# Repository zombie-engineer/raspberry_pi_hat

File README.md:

Raspberry PI hat.

Convenience expansion board for raspberry pi development.

Features:

JTAG connector for debug
Raspberry Pi has JTAG pins, TDO, TDI, TMS, TCK, etc. They are distributed in chaotic way across pin connector.
For this reason it is good to create a nice little connector, especially designated for JTAG

Micro USB connector for uart output
Raspberry PI has special pins for UART. This pins are routed to FTDI FT232H chip, which further redirects uart
data to USB.
Datasheet for the FTDI FT232H is here:
https://ftdichip.com/wp-content/uploads/2024/09/DS_FT232H.pdf

Display connector for ILI9341 SPI Display

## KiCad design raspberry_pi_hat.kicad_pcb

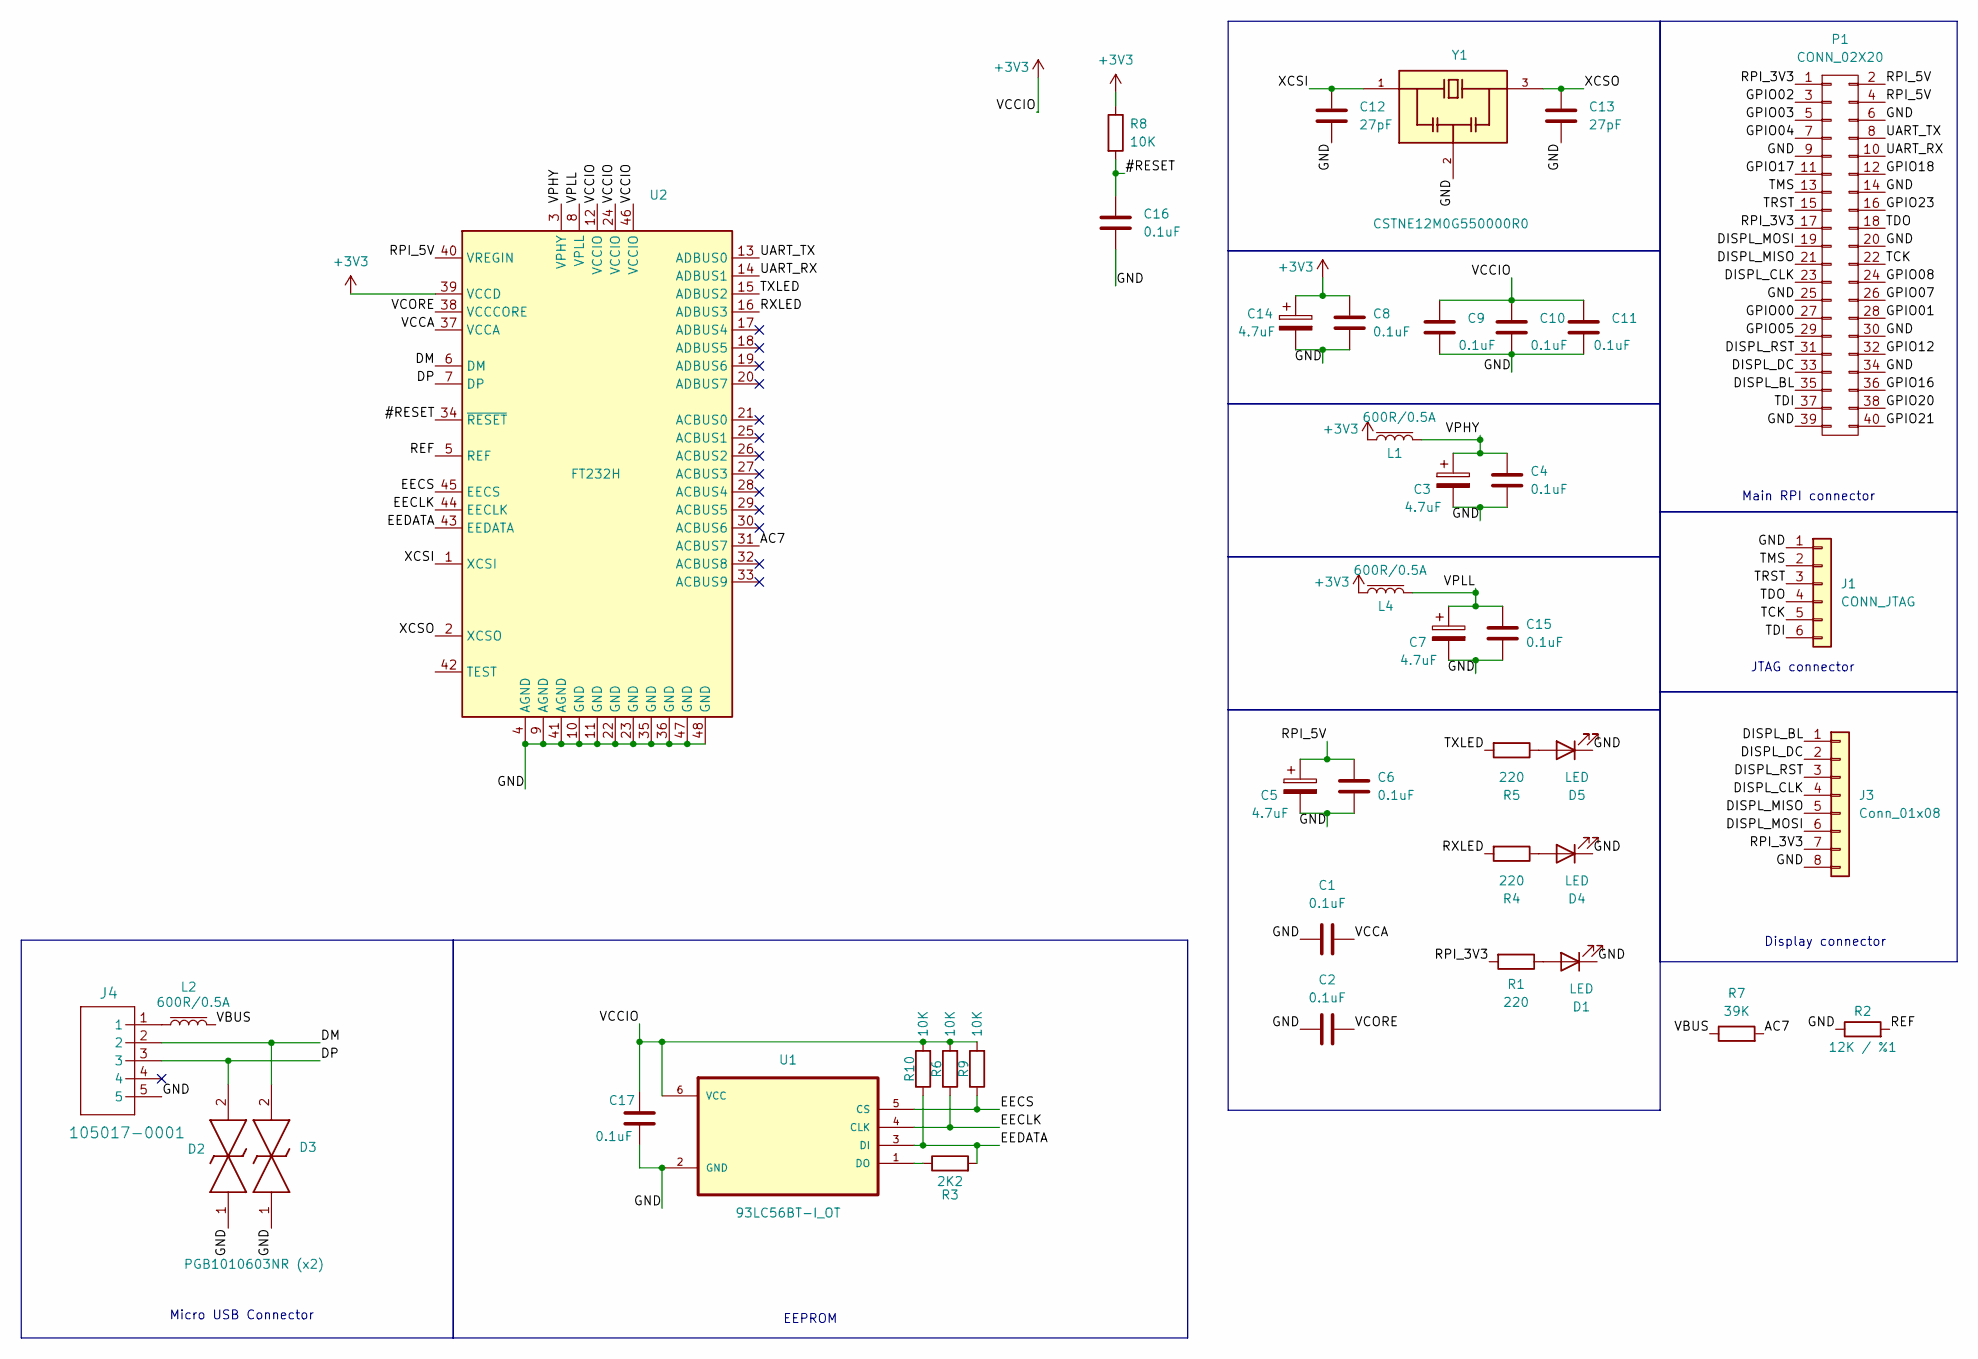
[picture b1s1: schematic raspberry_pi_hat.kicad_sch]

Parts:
C1, C2, C4, C6, C8, C9, C10, C11, C15, C16, C17: 0.1uF; C_0201_0603Metric_Pad0.64x0.40mm_HandSolder
C3, C5, C7, C14: 4.7uF; CAPPM2014X120N
C12, C13: 27pF; C_0201_0603Metric_Pad0.64x0.40mm_HandSolder
D1, D4, D5: LED; LED_0603_1608Metric
D2: PGB1010603NR (x2); PGB1010603NRHF; Mouser Part Number 576-PGB1010603NR
D3: PGB1010603NR; PGB1010603NRHF; Mouser Part Number 576-PGB1010603NR
J1: CONN_JTAG; PinSocket_1x06_P2.54mm_Horizontal
J3: Conn_01x08; PinHeader_1x08_P2.54mm_Horizontal
J4: 105017-0001; CON00363_5_MOL_FIXED
L1, L2, L4: 600R/0.5A; BLM21AG102BH1J
P1: CONN_02X20; PinSocket_2x20_P2.54mm_Vertical
R1, R4, R5: 220; R_0201_0603Metric_Pad0.64x0.40mm_HandSolder
R2: 12K / %1; R_0201_0603Metric_Pad0.64x0.40mm_HandSolder
R3: 2K2; R_0201_0603Metric_Pad0.64x0.40mm_HandSolder
R6, R8, R9, R10: 10K; R_0201_0603Metric_Pad0.64x0.40mm_HandSolder
R7: 39K; R_0201_0603Metric_Pad0.64x0.40mm_HandSolder
U1: 93LC56BT-I_OT; SOT95P280X145-6N
U2: FT232H; QFP50P900X900X160-48N
Y1: CSTNE12M0G550000R0; OSC_CSTNE12M0G550000R0; PARTREV JGC42-8858A

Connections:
+3V3: C8.1, C9.1, C10.1, C11.1, C14.1, C17.1, L1.1, L4.1, R6.2, R8.1, R9.2, R10.2, U1.6 (VCC), U2.12 (VCCIO), U2.24 (VCCIO), U2.39 (VCCD), U2.46 (VCCIO)
/#RESET: C16.1, R8.2, U2.34 (~RESET)
/AC7: R7.2, U2.31 (ACBUS7)
/DISPL_BL: J3.1, P1.35
/DISPL_CLK: J3.4, P1.23
/DISPL_DC: J3.2, P1.33
/DISPL_MISO: J3.5, P1.21
/DISPL_MOSI: J3.6, P1.19
/DISPL_RST: J3.3, P1.31
/DM: D3.2, J4.2, U2.6 (DM)
/DP: D2.2, J4.3, U2.7 (DP)
/EECLK: R6.1, U1.4 (CLK), U2.44 (EECLK)
/EECS: R9.1, U1.5 (CS), U2.45 (EECS)
/EEDATA: R3.2, R10.1, U1.3 (DI), U2.43 (EEDATA)
/GND: C1.1, C2.1, C3.2, C4.2, C5.2, C6.2, C7.2, C8.2, C9.2, C10.2, C11.2, C12.1, C13.1, C14.2, C15.2, C16.2, C17.2, D1.1 (K), D2.1, D3.1, D4.1 (K), D5.1 (K), J1.1, J3.8, J4.5, P1.6, P1.9, P1.14, P1.20, P1.25, P1.30, P1.34, P1.39, R2.1, U1.2 (GND), U2.4 (AGND), U2.9 (AGND), U2.10 (GND), U2.11 (GND), U2.22 (GND), U2.23 (GND), U2.35 (GND), U2.36 (GND), U2.41 (AGND), U2.47 (GND), U2.48 (GND), Y1.2
/GPIO00: P1.27
/GPIO01: P1.28
/GPIO02: P1.3
/GPIO03: P1.5
/GPIO04: P1.7
/GPIO05: P1.29
/GPIO07: P1.26
/GPIO08: P1.24
/GPIO12: P1.32
/GPIO16: P1.36
/GPIO17: P1.11
/GPIO18: P1.12
/GPIO20: P1.38
/GPIO21: P1.40
/GPIO23: P1.16
/REF: R2.2, U2.5 (REF)
/RPI_3V3: J3.7, P1.1, P1.17, R1.2
/RPI_5V: C5.1, C6.1, P1.2, P1.4, U2.40 (VREGIN)
/RXLED: R4.2, U2.16 (ADBUS3)
/TCK: J1.5, P1.22
/TDI: J1.6, P1.37
/TDO: J1.4, P1.18
/TMS: J1.2, P1.13
/TRST: J1.3, P1.15
/TXLED: R5.2, U2.15 (ADBUS2)
/UART_RX: P1.10, U2.14 (ADBUS1)
/UART_TX: P1.8, U2.13 (ADBUS0)
/VBUS: L2.2, R7.1
/VCCA: C1.2, U2.37 (VCCA)
/VCORE: C2.2, U2.38 (VCCCORE)
/VPHY: C3.1, C4.1, L1.2, U2.3 (VPHY)
/VPLL: C7.1, C15.1, L4.2, U2.8 (VPLL)
/XCSI: C12.2, U2.1 (XCSI), Y1.1
/XCSO: C13.2, U2.2 (XCSO), Y1.3
unnamed: D1.2 (A), R1.1
unnamed: D4.2 (A), R4.1
unnamed: D5.2 (A), R5.1
unnamed: J4.1, L2.1
unnamed: R3.1, U1.1 (DO)

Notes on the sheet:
Display connector
EEPROM
Main RPI connector
Micro USB Connector
JTAG connector

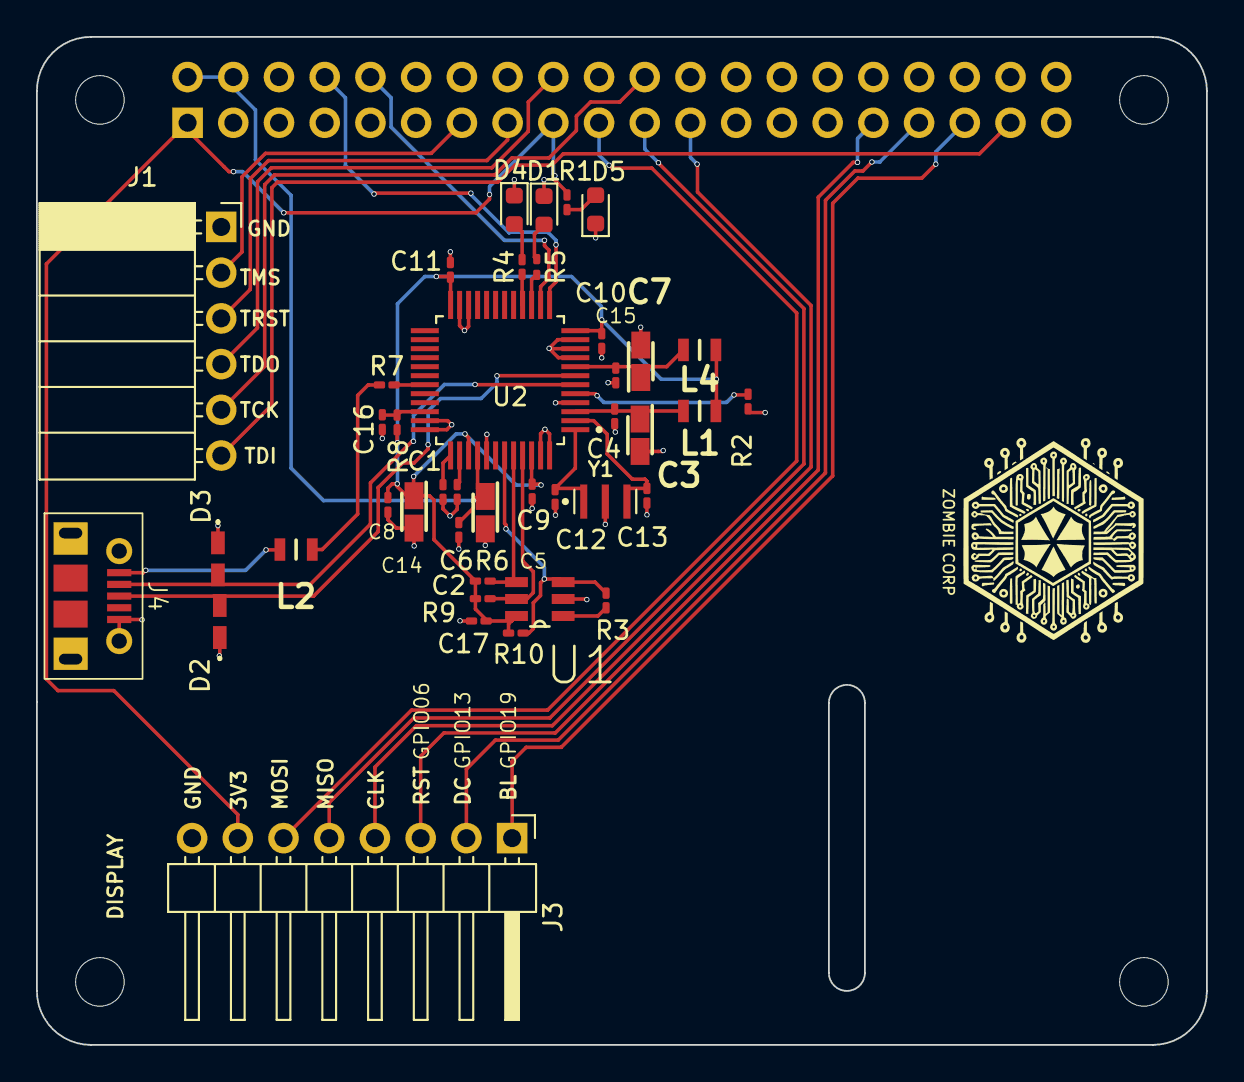
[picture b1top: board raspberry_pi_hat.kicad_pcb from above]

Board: 2 copper layers, 65.0 x 56.0 mm, 46 parts (1 on the bottom side), 39 nets.

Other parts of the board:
MK1, MK2, MK3, MK4: M2.5; MountingHole_2.7mm_M2.5

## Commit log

2025-02-22 init
2025-02-22 Added README.md
2025-02-22 progress
2025-02-22 Modified README.md
